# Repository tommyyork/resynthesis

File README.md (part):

# Resynthesis

This example implements a resynthesis effect for the Electro-Smith Daisy Patch.Init(), initially inspired by [the All Electric Smart Grid project](https://github.com/jvictor0/theallelectricsmartgrid) but it grew towards a granular direction as I added additional processing / while iterating on the output sounds. **This is maybe 90% GPT (🤖), 10% human, so buyer beware if you fork this or use this code.** There are plenty of bugs.

The panel design has most of the development hours, I wanted to procedurally generate it from the KiCad files for Patch.Init():

I've sent this off to the fab, and will make any updates once I've test fitted it on my actual Patch.Init(). Those labels for the pots may be too low...

The panel generation code could pretty easily be adapted to generate panels for any synth module, though the drill diameters and tolerances are currently hardcoded and basically tailored for the jacks / pots / switches you see in many Eurorack modules. The background pattern-to-pattern interpolation... I wish I could take credit. See [the agent session](AGENT_SESSION.md) for the blow by blow on how that came to be.

Incoming audio is analyzed into overlapping FFT grains, processed spectrally (phase propagation, V/OCT pitch, spectral flattening, bright/dark tilt, sparsity, and phase diffusion), and resynthesized with overlap-add back to the output. The V/OCT input (0–10 V) sets the fundamental frequency so the module can be used as an oscillator in a bass patch.

### Offline tests vs hardware signal path

The offline tests under `test/` are designed for **analysis and regressions**, not for level‑matched listening against the live module:

- **V/OCT harmonic tests (`make voct`, `test/test_resynth_voct.cpp`)**  
  - The processed passes are rendered **100% wet** with **no dry mix, no compressor, and no soft clip**.  
  - Grains are normalized only by hop size and active‑grain count, which keeps the **internal DSP stable** but typically yields WAVs that are **much quieter than the dry input**.  
  - This is intentional: the goal is **stable spectra and reliable note detection** (CSV/SVG analysis, suggested‑note checks), not loudness parity with the original sample or with the hardware output.

- **Harmonic engine tests (`make samples` → `test_resynth_harmonic`, `out/harmonic/*.wav`)**  
  - These also run the simplified harmonic resynth engine **fully wet** without the Patch‑SM output chain (no OFFER dry path, no post‑clip compressor, no panel‑driven MAX COMP).  
  - As a result, the harmonic test WAVs can also sit **significantly below** the level of the source material even though the spectra and pitch tracking match the intended behaviour.

- **Hardware firmware (`Resynthesis.cpp`)**  
  - On the Daisy Patch SM, the same core engine is wrapped in a **full output path**: OFFER dry/wet crossfade, hop/overlap‑aware wet gain smoothing, **smoothing‑dependent loudness compensation**, **soft clipping**, and a **fixed compressor/optional MAX COMP** stage.  
  - This chain is where the “finished instrument” loudness lives; the offline tests intentionally **omit** it so they can focus on **spectral behaviour, pitch stability, and CV‑to‑pitch mapping**.

If you A/B the `make voct` / harmonic WAVs against the original samples or the hardware output, expect them to be **significantly quieter**; treat them as **analysis fixtures**, not as loudness‑matched renderings of the module.

## Title: 化 (huà)

The panel uses the single character **化** (*huà*) as its primary title, from the *Daodejing* (道德經) in the sense of **transformation**—the change of one state into another, as in the phrase **化而欲作** (*huà ér yù zuò*, “when transformation arises, desire stirs”; ch. 37). Here it evokes the transformation of incoming sound through the phase vocoder into new timbres and textures.

**Panel typography:** All panel text is set in **all caps** using the open-source DIN-style font **[Gidole](https://github.com/larsenwork/Gidole)** (OFL licence; also available via [Google Fonts](https://fonts.google.com/specimen/Gidole)). The SVG uses the `Gidole` font family with fallbacks (DIN Alternate, DIN 2014, sans-serif) so the panel renders correctly even if Gidole is not installed.

## Make Targets

- **`make` / `make all`**: Build everything for this project (no tests are run): `libDaisy`, `DaisySP`, the `Resynthesis` firmware, host test binaries in `test/`, panel preview PNGs, and the SVG/PDF block‑diagram documentation.
- **`make program`**: Flash the built firmware image to the connected Daisy Patch SM.
- **`make openocd`**: Start OpenOCD for JTAG/SWD debug sessions.
- **`make debug`**: Build a debug firmware image and launch a GDB session against OpenOCD (with logging enabled as described below).
- **`make panel`**: Generate high‑resolution PNG previews of the front‑panel art in `panel/ResynthesisPanel.png` and `panel/ResynthesisPanel_eurorack_overlay.png` (requires Inkscape).
- **`make svg`**: Generate the US Letter block diagram of the audio path in `doc/Resynthesis_BlockDiagram_USLetter.pdf` and `doc/Resynthesis_BlockDiagram_USLetter.svg` (requires Graphviz `dot`).
- **`make test_resynth`**: Build and run the offline V/OCT sweep test; outputs WAVs into `test/out/voct_sweep/`.
- **`make test_cv_sweeps`**: Build and run the CV parameter sweep tests; outputs WAVs into `test/out/cv_sweep/` and `test/out/cv_sweep_maxcomp/`.
- **`make test_panel`**: Run the panel alignment / mechanical checks in `panel/test_panel_alignment.py`.
- **`make tests`**: Run the full test suite (`test_resynth`, `test_cv_sweeps`, and `test_panel`), regenerating WAVs under `test/out/`.
- **`make clean`**: Remove build artifacts and generated assets for this project (host test binaries, `test/out` WAVs, panel PNGs, and block‑diagram PDF/SVG/DOT files).

## Controls and panel mapping

This section is the **source of truth for panel labels and control behaviour**. Labels assume the **default CV bank** (no swapping).

### Potentiometers (CV_1–CV_4)

- **CV_1 – OFFER – send + dry/wet (panel: `OFFER`)**  
  Combined send and mix control for the resynthesis engine. **Fully CCW**, the output is **purely dry input** (non‑pitch‑shifted), and the engine effectively stops seeding new grains, so if no grains are currently active you hear a clean bypass. As you turn toward **12 o’clock**, the input is increasingly **“offered” to the grain engine** while a crossfade brings in the wet signal; around noon you get roughly **half dry, half wet** with the input actively feeding grains. **Fully CW** behaves like a **full send into the resynth path** so the output is dominated by loud, fully wet grains.  
  When **PITCH LOCK is on**, OFFER additionally becomes a **“pitch crossfade”**: CCW you hear the original, unshifted input; CW you hear a **clearly pitched, harmonically focused granular reconstruction** whose fundamental and partials follow the V/OCT voltage and **COLOR** setting, with most of the grain energy collapsing onto those harmonic families. Sweeping OFFER from CCW → CW in this case moves smoothly from dry, unshifted audio into the **fully pitch‑shifted, harmonically reinforced voice**, while existing grains are still allowed to **decay naturally** when you come back toward CCW.

- **CV_2 – Time‑Stretch / Grain Density (panel: `TIMESTRETCH`)**
  Bipolar control around 1× time. This knob controls how quickly grains are launched relative to the analysis hop: **left of centre** slows down and smears the audio into super‑slow, cloud‑like textures, while **right of centre** increases grain density and motion up into fast, chattery clusters. The mapping mirrors the TIME CV input so that the **0 V / noon region** covers the most musically useful 0.25×–4× range, with more extreme slow/fast behaviour toward the ends of travel.

- **CV_3 – FLUFF – granular cloud depth (panel: `FLUFF`)**  
  Sequentially enables a set of increasingly strong “cloud” behaviours in the grains. **Fully CCW** gives the most subtle, stable sound. As you turn clockwise, the engine adds:  
  1. Extra frequency‑dependent phase diffusion on top of CV_8.  
  2. Random jitter of the analysis window within each grain (time smearing) for a denser cloud.  
  3. Micro‑pitch jitter per grain in **pitch‑locked mode** (a few cents of movement around the target note).  
  4. Per‑bin magnitude jitter for a noisy, dense cloud at fully CW.  
  Existing spectral‑energy normalization keeps level changes musical across settings.

- **CV_4 – Color – bright/dark tilt, harmonic & frequency character (panel: `COLOR`)**  
  Three roles:
  - **Spectral tilt:** Negative values darken (emphasize low bins), positive values brighten (emphasize high bins); tilt gain is clamped so extremes do not clip or go silent.  
  - **Harmonic character in both modes (whenever PITCH LOCK is on):** **Color** selects which harmonic family is reinforced in **both** pitch‑locked and partial‑based modes using a **12‑harmonic scaffold** built on the V/OCT fundamental. **Fully CCW** emphasises the **even harmonics** \(2nd, 4th, 6th, … up to 12th\); around **noon** you get a more neutral mix; near **3 o’clock** and beyond the scaffold leans harder into the **odd harmonics**. Power is **front‑loaded into the low harmonics** and then tapered so that roughly the first four harmonics carry most of the added energy and higher harmonics contribute a progressively smaller, more textural sheen. In pitch‑locked mode the scaffold is gentler so the pitched grains stay dominant; in partial‑based mode the scaffold is more forward so simple inputs behave like a full synth voice. Reinforced partials use moderate, tapered gains so they **blend with the resynthesized body** rather than sounding like separate oscillators.  
  - **Pitch vs frequency shifting crossfade:** With PITCH LOCK on, the audio now passes through a dedicated **shifting block** immediately after the input. This block first **detects the incoming pitch** using a harmonic‑comb analyser (refactored from the offline V/OCT tests) and **pitch‑shifts** the input so its fundamental lands on the V/OCT‑selected note *before* any phase‑vocoder processing. As COLOR moves from roughly **3 o’clock to fully CW**, the block smoothly **fades from this pitch‑shifting process into a Bode‑style frequency shifter** whose shift rate also follows V/OCT. Fully CW gives a distinctly **frequency‑shifted, sideband‑style texture** feeding the resynth engine; backing off toward 3 o’clock restores more of the classic pitch‑locked behaviour.

### Toggles (B_7, B_8)

- **B_8 – PITCH LOCK (panel: `PITCH` / `LOCK`)**  
  Mode switch between **pitch‑locked grains** and a **partial‑based spectral model**:
  - **B_8 off – Partial‑based / spectral model mode**: Treats the incoming spectrum as a timbral template. Analysis bins stay at their original pitch; a **harmonic scaffold** (fundamental + harmonics) tuned to the **V/OCT** fundamental is overlaid with moderate gain so simple inputs behave like a full synth voice. **Color (CV_4)** selects the balance of odd vs even harmonics.  
  - **B_8 on – Pitch‑locked grains**: The phase‑vocoder pitch shifter locks each grain so its spectrum follows the V/OCT fundamental. This behaves more like a traditional pitched oscillator with the input acting as a complex waveform; the **same harmonic scaffold** is now applied more gently on top, reinforcing the chosen harmonic family without overwhelming the pitch‑corrected grains.

- **B_7 – MAX COMP (panel: `MAX` / `COMP`)**  
  Toggles a **stronger “MAX COMP” output compressor** after the resynth engine:
  - **Hardware:** B_7 is a **momentary pushbutton**, but the firmware treats it as a **software toggle**: each press flips the MAX COMP state between off and on.  
  - **B_7 off – Normal compression**: A gentle **2:1 feedforward compressor** (threshold ≈ -12 dB, modest make‑up gain) keeps levels musical and consistent as a sound source without being too squashy.  
  - **B_7 on – MAX COMP**: A more aggressive **Omnipressor‑style setting** (negative ratio, higher make‑up gain) that keeps average loudness high and brings out quiet material; this matches the “MAX COMP” path used in the offline CV sweep tests (`test/out/cv_sweep_maxcomp/`). When MAX COMP is active, the **front‑panel status LED above the jacks blinks at roughly 1 Hz** to indicate that the software toggle is engaged.

### CV inputs (CV_5–CV_8, middle jack row)

The middle jack row (panel labels above the jacks) is:

- `V/OCT`, `SMOOTH`, `SPARSITY`, *`D`* (diffusion)

Mapped controls:

- **CV_5 – V/OCT (panel: `V/OCT`, 0–10 V, 1 V/oct)**  
  Volt‑per‑octave pitch control. In both modes the algorithm resynthesizes the input around a musical fundamental set by this voltage (e.g. 1 V ≈ 32.7 Hz / C1, 2 V ≈ 65.4 Hz / C2). In **pitch‑locked mode** the new **shifting block** and the phase‑vocoder engine both treat this as the target note: the block first **shifts the raw input** so its detected fundamental lands on the requested V/OCT pitch, and the phase‑vocoder then follows that same fundamental when mapping grains; in **partial‑based mode** the original spectrum stays nearer its analysed pitch while a more forward harmonic scaffold (fundamental + harmonics) is overlaid at the V/OCT frequency.  
  With PITCH LOCK on and OFFER turned up, the combination of the shifting block and harmonic scaffold now **focuses most of the spectral energy into the fundamental and harmonics implied by V/OCT and COLOR** so the result is a **grainy but clearly pitched voice** rather than a diffuse, purely formant‑style texture. At the very top of COLOR, that same V/OCT value instead drives the **frequency‑shift amount** in the Bode‑style shifter, giving inharmonic, sideband‑rich tones feeding the resynth stage. 0 V = C0 (~16.35 Hz); 10 V is internally clamped near the upper range.

- **CV_6 – Magnitude Smoothing (panel: `SMOOTH`, bipolar, -5 V to +5 V)**  
  Controls how quickly spectral magnitudes follow the input. **Low** voltages track transients closely (crisp, articulate); **high** voltages smear dynamics into a pad‑like magnitude envelope. The engine’s **default** smoothing is now around **0.2**, which keeps transients present while still allowing the adaptive smoothing stages to build a stable, cloud‑like body at higher settings.

- **CV_7 – Spectral Sparsity (panel: `SPARSITY`, bipolar, -5 V to +5 V)**  
  Bipolar control mapped to the full **0–1** sparsity range (0 V ≈ 0.5). Lower values keep most bins active and sound fuller; higher values keep only the strongest bins, leading to more pronounced, metallic / ring‑mod‑like spectra, with internal energy preservation so results stay present rather than simply “thin”.

- **CV_8 – Phase Diffusion (panel: italic `D`, bipolar, -5 V to +5 V)**  
  Bipolar control mapped to the full **0–1** diffusion range (0 V ≈ 0.5). Lower values keep phases more coherent (clearer tone); higher values introduce strong randomization for noisy, cloud‑like, frequency‑shift‑ish textures. **FLUFF (CV_3)** can add extra diffusion on top of this control.

### CV outputs (CV_OUT_1, CV_OUT_2)

- **CV_OUT_1 / C10 – THOUGHTS (panel: lightning bolt symbol `⚡`)**  
  CV jack directly beneath the COLOR knob (top‑right of the middle‑switch/jack cluster).  
  - **Signal:** A **chaotic, Brownian‑like CV** that wanders in a musically bounded way between 0–5 V. Its motion becomes **wider and quicker** when the input is loud and harmonically rich, and **slower and more restrained** when the input is quieter and more noise‑like or spectrally flat.  
  - **Construction:** Internally, THOUGHTS is driven by a **logistic‑map–style chaotic system**. Each audio frame, the engine measures both a smoothed spectral‑energy value and a simple **harmonic peakiness metric** (how “spiky” the spectrum is relative to its mean). These two features form an **excitement** value that modulates the chaotic map’s parameter and effective step rate, then the result is centered, range‑scaled by excitement, and gently low‑pass filtered before being mapped to 0–5 V.  
  - **Musical uses:** Because THOUGHTS reacts to both loudness and harmonic structure but with an internal chaotic drift, it behaves as an **interesting, somewhat tangential CV source**: ideal for slowly moving filter cutoffs, effect depths, wavefolder thresholds, or other processors that you want to “breathe” with the resynth texture without being a simple envelope follower. High‑energy, harmonic material produces animated, complex CV excursions; sparse or dark inputs yield smaller, slower meanders that still feel alive.

- **CV_OUT_2 – Grain energy meter + MAX COMP status / LED driver (no dedicated panel label)**  
  Drives the **front‑panel status LED** (row “LED (status)” in the jack/part mapping table) and exposes a **0–5 V envelope of the grain engine’s activity**, with a **MAX COMP blink overlay**:  
  - **Base behaviour (MAX COMP off):** CV_OUT_2 follows the current **grain / spectral energy** of the resynthesis engine, mapped into **0–5 V**. Quiet, sparse material produces a dim LED / low CV; louder, denser inputs push the LED and CV level towards 5 V.  
  - **MAX COMP on (software toggle engaged):** The same grain‑energy envelope continues to drive CV_OUT_2, but a **logic‑style overlay blinks the output at full intensity (~1.5 Hz)** to show that MAX COMP is active. During the “on” phase of the blink the output is forced to **5 V**; during the “off” phase it returns to the underlying grain‑energy level.  
  This output is intended primarily for the on‑panel LED, but you can patch it elsewhere either as a **grain‑energy envelope follower** or as a **MAX COMP activity indicator**. Its behaviour is independent of **THOUGHTS (CV_OUT_1)**, which continues to carry the separate chaotic CV derived from the same internal analysis.

### Jacks: gates, CVs, and audio I/O

Panel jack layout (from top row to bottom row; labels are **over** each jack and centered):

- **Top row** (4 jacks): `B10`, `B9`, `B5`, `B6` — gate inputs/outputs.
- **Middle row** (4 jacks): `V/OCT` (CV_5), *`t`* / TIME (CV_6), `SPARSITY` (CV_7), *`D`* / diffusion (CV_8).
- **Bottom row** (4 jacks): `IN L`, `IN R`, `OUT L`, `OUT R` — stereo audio inputs and outputs. The two middle jacks are also **CV_OUT_1** and **CV_OUT_2** in firmware.

### Stereo inputs and outputs

- **IN L / IN R (bottom row, left two jacks; panel: `IN L`, `IN R`)**  
  Audio inputs mapped to firmware channels `IN_L` and `IN_R`. They feed the analysis stage of the phase vocoder; typical use is a stereo source (e.g. a loop, synth, or external instrument).

- **OUT L / OUT R (bottom row, right two jacks; panel: `OUT L`, `OUT R`)**  
  Audio outputs mapped to firmware channels `OUT_L` and `OUT_R`. Carry the fully processed resynth signal after shaping, overlap‑add synthesis, soft clipping, and final compressor. Useful both as **effect returns** and as a standalone stereo sound source when driven from V/OCT.

## Panel

### Files

- **`panel/output/ResynthesisPanel.svg`**  
  Vector artwork of a 3U x 10HP Eurorack panel: height **128.5 mm**, width **50.8 mm**. All graphics and drill holes are in millimetres. **Generated by** `panel/_deprecated_generate_panel.py` (or `panel/generate_panel_kicad.py`).

- **`panel/output/ResynthesisPanel.jpg`**  
  Single panel preview image for quick visual reference. Generated from `ResynthesisPanel.svg` by `make panel` (requires Inkscape).

- **`panel/output/render_eurorack_overlay.py`**  
  Script that generates an **Eurorack standard overlay** SVG from any panel SVG: green dotted 2HP vertical grid, neon blue dotted rail‑center lines, neon pink (x, y) annotations at each cut center plus panel dimensions.

- **`panel/_deprecated_generate_panel.py`**  
  Deprecated Python script that generates the canonical `ResynthesisPanel.svg` (prefer `panel/generate_panel_kicad.py`). It encodes the full 3U × 10HP geometry, background artwork, all drill centres, the SD card holder cutout, and the four rectangular Eurorack mounting screw slots so they line up with the Doepfer / Gie‑Tec rail standard (3 mm from the top and bottom edges; see `panel/eurorack_spec/README.md`).

### Input / jack mapping (KiCad PCB → panel)

The table below ties together the **Resynthesis panel labels**, the **Patch.Init default panel silkscreen**, the **KiCad schematic references**, and the mechanical information from the KiCad footprints. Positions are given in KiCad PCB coordinates (millimetres) taken from `panel/KiCad_PCB/ES_Daisy_Patch_SM_FB_Rev1.kicad_pcb`.

| Resynthesis label   | Patch.Init panel label | Component type          | Panel hole Ø (mm) | PCB X (mm) | PCB Y (mm) | KiCad schematic ref | Footprint filename                  |
|---------------------|------------------------|-------------------------|-------------------|------------|------------|----------------------|-------------------------------------|
| B10 (gate in 1)     | B10                    | S_JACK                  | 6.2               | 130.251    | 125.316    | J_GATEIN1            | `S_JACK.kicad_mod`                  |
| B9 (gate in 2)      | B9                     | S_JACK                  | 6.2               | 142.418    | 125.316    | J_GATEIN2            | `S_JACK.kicad_mod`                  |
| B5 (gate out 1)     | B5                     | S_JACK                  | 6.2               | 154.584    | 125.316    | J_GATEOUT1           | `S_JACK.kicad_mod`                  |
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
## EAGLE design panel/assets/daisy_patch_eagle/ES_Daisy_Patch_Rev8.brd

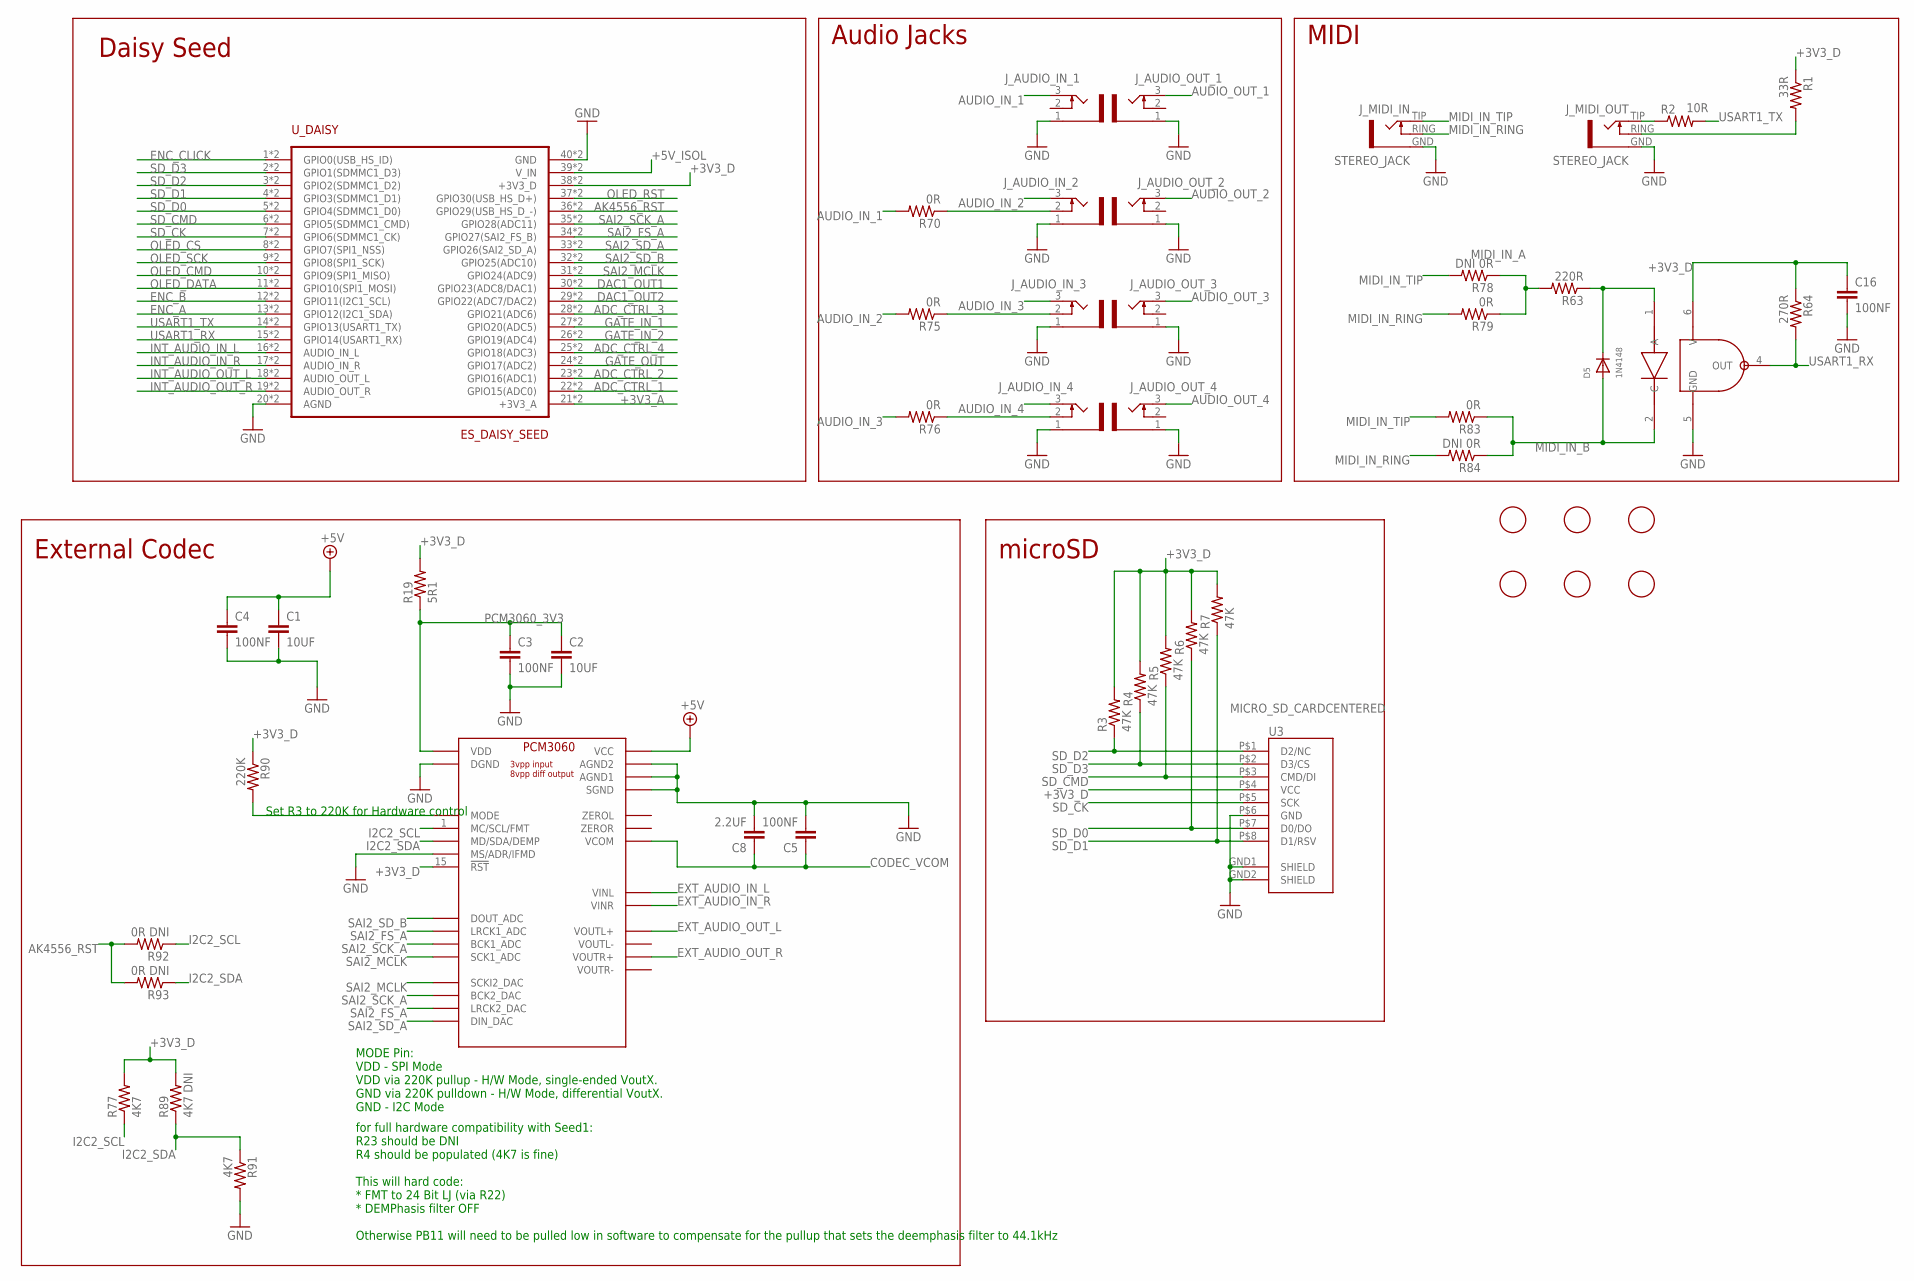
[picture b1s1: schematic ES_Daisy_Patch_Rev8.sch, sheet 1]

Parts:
C1, C2: 10UF; C0805
C3, C4, C5, C16: 100NF; C0402
C8: 2.2UF; C0603
D5: 1N4148; SOD-323F
FD1, FD2, FD3, FD4, FD5, FD6: FIDUCIAL; FIDUCIAL_1MM
J_AUDIO_IN_1, J_AUDIO_IN_2, J_AUDIO_IN_3, J_AUDIO_IN_4: EURO_JACK_SMT; SMT_JACK
J_AUDIO_OUT_1, J_AUDIO_OUT_2, J_AUDIO_OUT_3, J_AUDIO_OUT_4: EURO_JACK_SMT; SMT_JACK
J_MIDI_IN: STEREO_JACK; STEREO_JACK_3.5MM
J_MIDI_OUT: STEREO_JACK; STEREO_JACK_3.5MM
R1: 33R; R0603
R2: 10R; R0603
R3, R4, R5, R6, R7: 47K; R0603
R19: 5R1; R0603
R63: 220R; R0603
R64: 270R; R0603
R70, R75, R76, R79, R83: 0R; R0603
R77, R91: 4K7; R0603
R78, R84: DNI 0R; R0603
R89: 4K7 DNI; R0603
R90: 220K; R0603
R92, R93: 0R DNI; R0603
U1: PCM3060; TSSOP-28
U3: MICRO_SD_CARDCENTERED; VERT_MICROSD_CENTERED
U15: OPTOISOLATOR_H11L1M; DIL06_GULLWING
U_DAISY: ES_DAISY_SEED; ES_DAISY_SEED_DOUBLE

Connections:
+3V3_A: U_DAISY.21 (+3V3_A), U_DAISY.B21 (+3V3_A); also elsewhere on the board
+3V3_D: C16.1, R1.1, R3.2, R4.2, R5.2, R6.2, R7.2, R19.2, R64.1, R77.2, R89.2, R90.1, U1.15 (!RST), U3.P$4 (VCC), U15.6 (V), U_DAISY.38 (+3V3_D), U_DAISY.B38 (+3V3_D); also elsewhere on the board
+5V: C1.1, C4.1, U1.24 (VCC); also elsewhere on the board
+5V_ISOL: U_DAISY.39 (V_IN), U_DAISY.B39 (V_IN); also elsewhere on the board
ADC_CTRL_1: U_DAISY.22 (GPIO15(ADC0)), U_DAISY.B22 (GPIO15(ADC0)); also elsewhere on the board
ADC_CTRL_2: U_DAISY.23 (GPIO16(ADC1)), U_DAISY.B23 (GPIO16(ADC1)); also elsewhere on the board
ADC_CTRL_3: U_DAISY.28 (GPIO21(ADC6)), U_DAISY.B28 (GPIO21(ADC6)); also elsewhere on the board
ADC_CTRL_4: U_DAISY.25 (GPIO18(ADC3)), U_DAISY.B25 (GPIO18(ADC3)); also elsewhere on the board
AK4556_RST: R92.2, R93.2, U_DAISY.36 (GPIO29(USB_HS_D_-)), U_DAISY.B36 (GPIO29(USB_HS_D_-))
AUDIO_IN_1: J_AUDIO_IN_1.3 (TIP), R70.2; also elsewhere on the board
AUDIO_IN_2: J_AUDIO_IN_2.3 (TIP), R75.2; also elsewhere on the board
AUDIO_IN_3: J_AUDIO_IN_3.3 (TIP), R76.2; also elsewhere on the board
AUDIO_IN_4: J_AUDIO_IN_4.3 (TIP); also elsewhere on the board
AUDIO_OUT_1: J_AUDIO_OUT_1.3 (TIP); also elsewhere on the board
AUDIO_OUT_2: J_AUDIO_OUT_2.3 (TIP); also elsewhere on the board
AUDIO_OUT_3: J_AUDIO_OUT_3.3 (TIP); also elsewhere on the board
AUDIO_OUT_4: J_AUDIO_OUT_4.3 (TIP); also elsewhere on the board
CODEC_VCOM: C5.1, C8.1, U1.21 (VCOM); also elsewhere on the board
DAC1_OUT1: U_DAISY.30 (GPIO23(ADC8/DAC1)), U_DAISY.B30 (GPIO23(ADC8/DAC1)); also elsewhere on the board
DAC1_OUT2: U_DAISY.29 (GPIO22(ADC7/DAC2)), U_DAISY.B29 (GPIO22(ADC7/DAC2)); also elsewhere on the board
ENC_A: U_DAISY.13 (GPIO12(I2C1_SDA)), U_DAISY.B13 (GPIO12(I2C1_SDA)); also elsewhere on the board
ENC_B: U_DAISY.12 (GPIO11(I2C1_SCL)), U_DAISY.B12 (GPIO11(I2C1_SCL)); also elsewhere on the board
ENC_CLICK: U_DAISY.1 (GPIO0(USB_HS_ID)), U_DAISY.B1 (GPIO0(USB_HS_ID)); also elsewhere on the board
EXT_AUDIO_IN_L: U1.25 (VINL); also elsewhere on the board
EXT_AUDIO_IN_R: U1.26 (VINR); also elsewhere on the board
EXT_AUDIO_OUT_L: U1.20 (VOUTL+); also elsewhere on the board
EXT_AUDIO_OUT_R: U1.18 (VOUTR+); also elsewhere on the board
GATE_IN_1: U_DAISY.27 (GPIO20(ADC5)), U_DAISY.B27 (GPIO20(ADC5)); also elsewhere on the board
GATE_IN_2: U_DAISY.26 (GPIO19(ADC4)), U_DAISY.B26 (GPIO19(ADC4)); also elsewhere on the board
GATE_OUT: U_DAISY.24 (GPIO17(ADC2)), U_DAISY.B24 (GPIO17(ADC2)); also elsewhere on the board
GND: C1.2, C2.2, C3.2, C4.2, C5.2, C8.2, C16.2, J_AUDIO_IN_1.1 (GND), J_AUDIO_IN_2.1 (GND), J_AUDIO_IN_3.1 (GND), J_AUDIO_IN_4.1 (GND), J_AUDIO_OUT_1.1 (GND), J_AUDIO_OUT_2.1 (GND), J_AUDIO_OUT_3.1 (GND), J_AUDIO_OUT_4.1 (GND), J_MIDI_IN.GND, J_MIDI_OUT.GND, R91.2, U1.8 (DGND), U1.16 (SGND), U1.22 (AGND2), U1.23 (AGND1), U1.27 (MS/ADR/IFMD), U3.GND1 (SHIELD), U3.GND2 (SHIELD), U3.P$6 (GND), U15.5 (GND), U_DAISY.20 (AGND), U_DAISY.40 (GND), U_DAISY.B20 (AGND), U_DAISY.B40 (GND); also elsewhere on the board
I2C2_SCL: R77.1, R92.1, U1.1 (MC/SCL/FMT)
I2C2_SDA: R89.1, R91.1, R93.1, U1.2 (MD/SDA/DEMP)
INT_AUDIO_IN_L: U_DAISY.16 (AUDIO_IN_L), U_DAISY.B16 (AUDIO_IN_L); also elsewhere on the board
INT_AUDIO_IN_R: U_DAISY.17 (AUDIO_IN_R), U_DAISY.B17 (AUDIO_IN_R); also elsewhere on the board
INT_AUDIO_OUT_L: U_DAISY.18 (AUDIO_OUT_L), U_DAISY.B18 (AUDIO_OUT_L); also elsewhere on the board
INT_AUDIO_OUT_R: U_DAISY.19 (AUDIO_OUT_R), U_DAISY.B19 (AUDIO_OUT_R); also elsewhere on the board
MIDI_IN_A: R63.2, R78.1, R79.1
MIDI_IN_B: D5.A, R83.1, R84.1, U15.2 (C)
MIDI_IN_RING: J_MIDI_IN.RING (NORM), R79.2, R84.2
MIDI_IN_TIP: J_MIDI_IN.TIP, R78.2, R83.2
unnamed: J_MIDI_OUT.TIP, R2.1
unnamed: J_MIDI_OUT.RING (NORM), R1.2
unnamed: J_AUDIO_IN_2.2 (NORM), R70.1
unnamed: J_AUDIO_IN_3.2 (NORM), R75.1
unnamed: J_AUDIO_IN_4.2 (NORM), R76.1
unnamed: R90.2, U1.28 (MODE)
unnamed: D5.C, R63.1, U15.1 (A)
OLED_CMD: U_DAISY.10 (GPIO9(SPI1_MISO)), U_DAISY.B10 (GPIO9(SPI1_MISO)); also elsewhere on the board
OLED_CS: U_DAISY.8 (GPIO7(SPI1_NSS)), U_DAISY.B8 (GPIO7(SPI1_NSS)); also elsewhere on the board
OLED_DATA: U_DAISY.11 (GPIO10(SPI1_MOSI)), U_DAISY.B11 (GPIO10(SPI1_MOSI)); also elsewhere on the board
OLED_RST: U_DAISY.37 (GPIO30(USB_HS_D+)), U_DAISY.B37 (GPIO30(USB_HS_D+)); also elsewhere on the board
OLED_SCK: U_DAISY.9 (GPIO8(SPI1_SCK)), U_DAISY.B9 (GPIO8(SPI1_SCK)); also elsewhere on the board
PCM3060_3V3: C2.1, C3.1, R19.1, U1.7 (VDD)
SAI2_FS_A: U1.4 (LRCK1_ADC), U1.11 (LRCK2_DAC), U_DAISY.34 (GPIO27(SAI2_FS_B)), U_DAISY.B34 (GPIO27(SAI2_FS_B))
SAI2_MCLK: U1.6 (SCK1_ADC), U1.9 (SCKI2_DAC), U_DAISY.31 (GPIO24(ADC9)), U_DAISY.B31 (GPIO24(ADC9))
SAI2_SCK_A: U1.5 (BCK1_ADC), U1.10 (BCK2_DAC), U_DAISY.35 (GPIO28(ADC11)), U_DAISY.B35 (GPIO28(ADC11))
SAI2_SD_A: U1.12 (DIN_DAC), U_DAISY.33 (GPIO26(SAI2_SD_A)), U_DAISY.B33 (GPIO26(SAI2_SD_A))
SAI2_SD_B: U1.3 (DOUT_ADC), U_DAISY.32 (GPIO25(ADC10)), U_DAISY.B32 (GPIO25(ADC10))
SD_CK: U3.P$5 (SCK), U_DAISY.7 (GPIO6(SDMMC1_CK)), U_DAISY.B7 (GPIO6(SDMMC1_CK))
SD_CMD: R5.1, U3.P$3 (CMD/DI), U_DAISY.6 (GPIO5(SDMMC1_CMD)), U_DAISY.B6 (GPIO5(SDMMC1_CMD))
SD_D0: R6.1, U3.P$7 (D0/DO), U_DAISY.5 (GPIO4(SDMMC1_D0)), U_DAISY.B5 (GPIO4(SDMMC1_D0))
SD_D1: R7.1, U3.P$8 (D1/RSV), U_DAISY.4 (GPIO3(SDMMC1_D1)), U_DAISY.B4 (GPIO3(SDMMC1_D1))
SD_D2: R3.1, U3.P$1 (D2/NC), U_DAISY.3 (GPIO2(SDMMC1_D2)), U_DAISY.B3 (GPIO2(SDMMC1_D2))
SD_D3: R4.1, U3.P$2 (D3/CS), U_DAISY.2 (GPIO1(SDMMC1_D3)), U_DAISY.B2 (GPIO1(SDMMC1_D3))
USART1_RX: R64.2, U15.4 (OUT), U_DAISY.15 (GPIO14(USART1_RX)), U_DAISY.B15 (GPIO14(USART1_RX))
USART1_TX: R2.2, U_DAISY.14 (GPIO13(USART1_TX)), U_DAISY.B14 (GPIO13(USART1_TX))

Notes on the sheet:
Daisy Seed
Audio Jacks
External Codec
MIDI
microSD
MODE Pin: VDD - SPI Mode VDD via 220K pullup - H/W Mode, single-ended VoutX. GND via 220K pulldown - H/W Mode, differential VoutX. GND - I2C Mode
Set R3 to 220K for Hardware control
for full hardware compatibility with Seed1: R23 should be DNI R4 should be populated (4K7 is fine) This will hard code: * FMT to 24 Bit LJ (via R22) * DEMPhasis filter OFF Otherwise PB11 will need to be pulled low in software to compensate for the pullup that sets the deemphasis filter to 44.1kHz

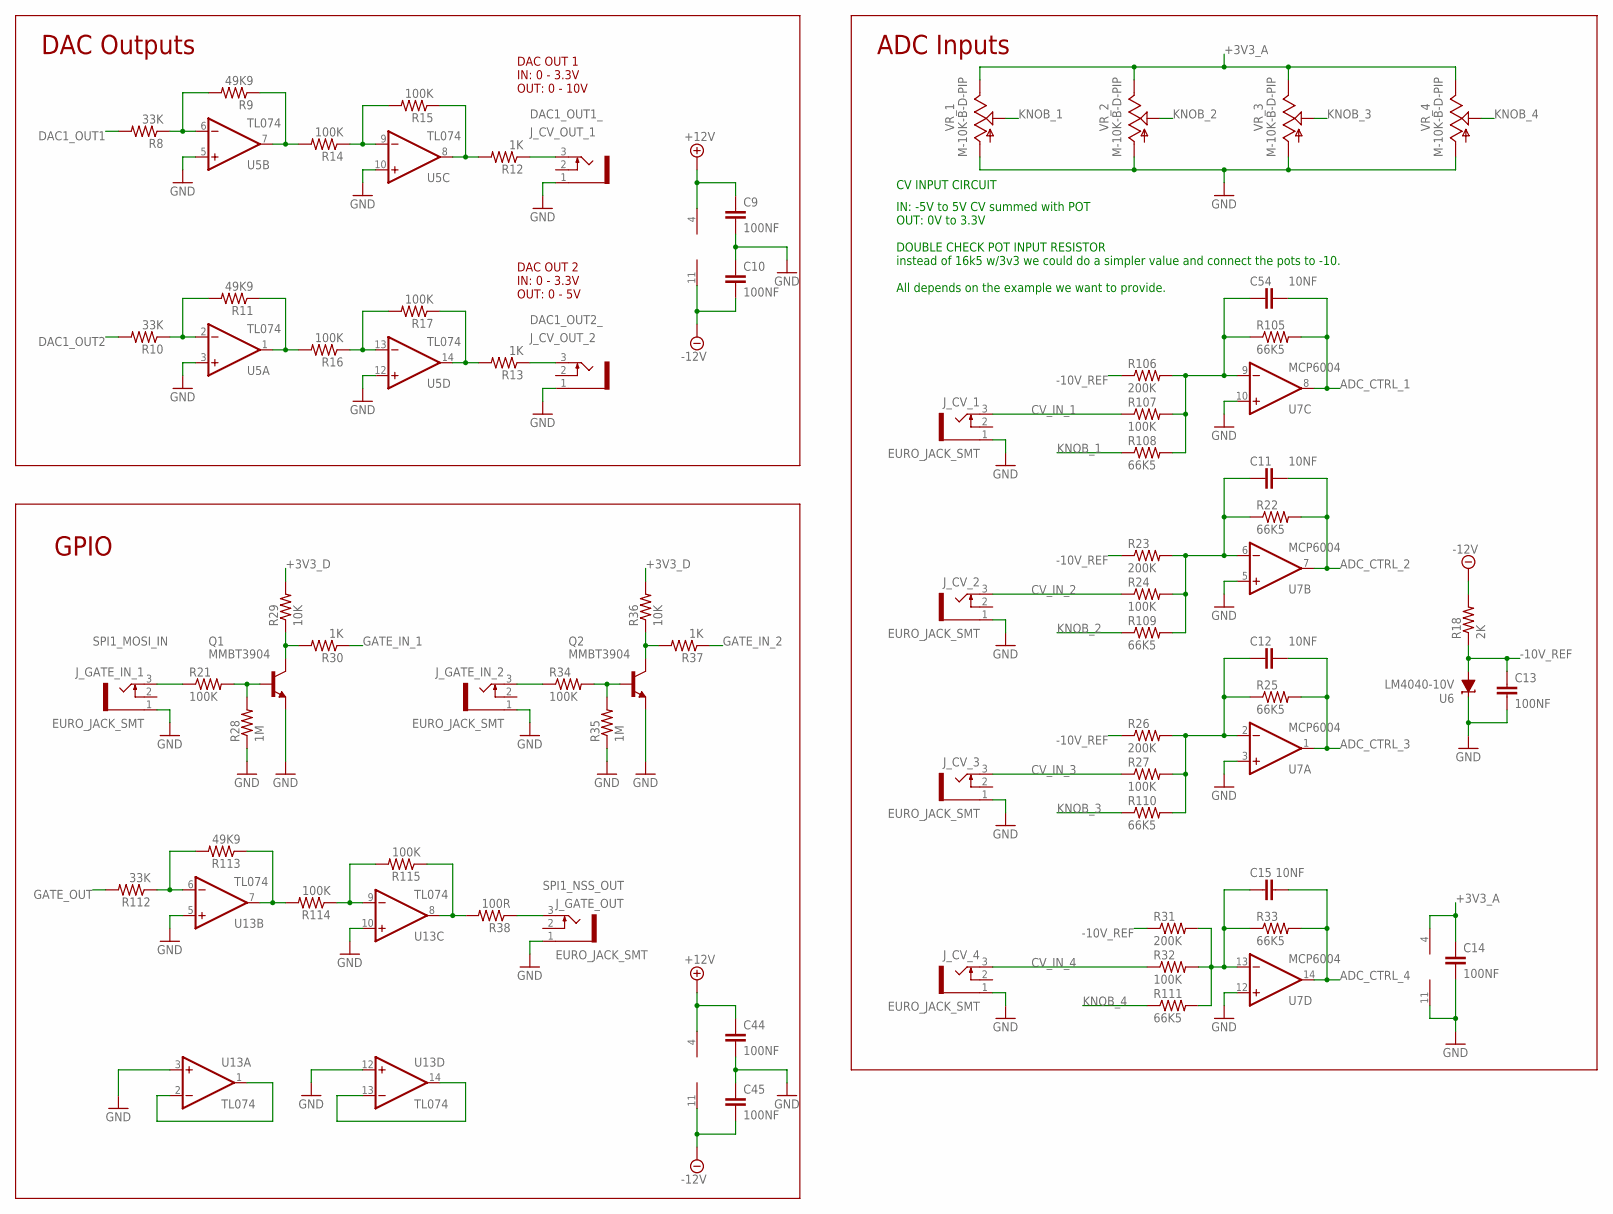
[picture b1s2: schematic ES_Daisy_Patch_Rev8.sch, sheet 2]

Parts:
C9, C10, C13, C14, C44, C45: 100NF; C0402
C11, C12, C15, C54: 10NF; C0603
J_CV_1, J_CV_2, J_CV_3, J_CV_4: EURO_JACK_SMT; SMT_JACK
J_CV_OUT_1, J_CV_OUT_2: EURO_JACK_SMT; SMT_JACK
J_GATE_IN_1, J_GATE_IN_2: EURO_JACK_SMT; SMT_JACK
J_GATE_OUT: EURO_JACK_SMT; SMT_JACK
Q1, Q2: MMBT3904; SOT23-BEC
R8, R10, R112: 33K; R0603
R9, R11, R113: 49K9; R0603
R12, R13, R30, R37: 1K; R0402
R14, R15, R16, R17, R21, R24, R27, R32, R34, R107, R114, R115: 100K; R0402
R18: 2K; R0603
R22, R25, R33, R105, R108, R109, R110, R111: 66K5; R0603
R23, R26, R31, R106: 200K; R0603
R28, R35: 1M; R0603
R29, R36: 10K; R0603
R38: 100R; R0603
U5, U13: TL074; TSSOP-14
U6: LM4040-10V; DBZ_R-PDSO-G3
U7: MCP6004; TSSOP-14
VR_1, VR_2, VR_3, VR_4: M-10K-B-D-PIP; PIP_POT_PASTE6

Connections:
+3V3_A: C14.1, U7.4 (V+), VR_1.3, VR_2.3, VR_3.3, VR_4.3; also elsewhere on the board
+3V3_D: R29.2, R36.2; also elsewhere on the board
+12V: C9.1, C44.1, U5.4 (V+), U13.4 (V+); also elsewhere on the board
-10V_REF: C13.1, R18.1, R23.1, R26.1, R31.1, R106.1, U6.2 (A)
-12V: C10.2, C45.2, R18.2, U5.11 (V-), U13.11 (V-); also elsewhere on the board
ADC_CTRL_1: C54.2, R105.2, U7.8 (OUT); also elsewhere on the board
ADC_CTRL_2: C11.2, R22.2, U7.7 (OUT); also elsewhere on the board
ADC_CTRL_3: C12.2, R25.2, U7.1 (OUT); also elsewhere on the board
ADC_CTRL_4: C15.2, R33.2, U7.14 (OUT); also elsewhere on the board
CV_IN_1: J_CV_1.3 (TIP), R107.1
CV_IN_2: J_CV_2.3 (TIP), R24.1
CV_IN_3: J_CV_3.3 (TIP), R27.1
CV_IN_4: J_CV_4.3 (TIP), R32.1
DAC1_OUT1: R8.2; also elsewhere on the board
DAC1_OUT1_: J_CV_OUT_1.3 (TIP), R12.1
DAC1_OUT2: R10.2; also elsewhere on the board
DAC1_OUT2_: J_CV_OUT_2.3 (TIP), R13.1
GATE_IN_1: R30.1; also elsewhere on the board
GATE_IN_2: R37.1; also elsewhere on the board
GATE_OUT: R112.2; also elsewhere on the board
GND: C9.2, C10.1, C13.2, C14.2, C44.2, C45.1, J_CV_1.1 (GND), J_CV_2.1 (GND), J_CV_3.1 (GND), J_CV_4.1 (GND), J_CV_OUT_1.1 (GND), J_CV_OUT_2.1 (GND), J_GATE_IN_1.1 (GND), J_GATE_IN_2.1 (GND), J_GATE_OUT.1 (GND), Q1.E, Q2.E, R28.1, R35.1, U5.3 (+IN), U5.5 (+IN), U5.10 (+IN), U5.12 (+IN), U6.1 (C), U7.3 (+IN), U7.5 (+IN), U7.10 (+IN), U7.11 (V-), U7.12 (+IN), U13.3 (+IN), U13.5 (+IN), U13.10 (+IN), U13.12 (+IN), VR_1.1, VR_2.1, VR_3.1, VR_4.1; also elsewhere on the board
KNOB_1: R108.1, VR_1.2
KNOB_2: R109.1, VR_2.2
KNOB_3: R110.1, VR_3.2
KNOB_4: R111.1, VR_4.2
unnamed: R14.1, R15.2, U5.9 (-IN)
unnamed: R12.2, R15.1, U5.8 (OUT)
unnamed: R8.1, R9.2, U5.6 (-IN)
unnamed: R9.1, R14.2, U5.7 (OUT)
unnamed: C54.1, R105.1, R106.2, R107.2, R108.2, U7.9 (-IN)
unnamed: R10.1, R11.2, U5.2 (-IN)
unnamed: R11.1, R16.2, U5.1 (OUT)
unnamed: R112.1, R113.2, U13.6 (-IN)
unnamed: R16.1, R17.2, U5.13 (-IN)
unnamed: R13.2, R17.1, U5.14 (OUT)
unnamed: U13.1 (OUT), U13.2 (-IN)
unnamed: R113.1, R114.2, U13.7 (OUT)
unnamed: R114.1, R115.2, U13.9 (-IN)
unnamed: R38.2, R115.1, U13.8 (OUT)
unnamed: Q1.C, R29.1, R30.2
unnamed: C11.1, R22.1, R23.2, R24.2, R109.2, U7.6 (-IN)
unnamed: Q2.B, R34.2, R35.2
unnamed: C12.1, R25.1, R26.2, R27.2, R110.2, U7.2 (-IN)
unnamed: Q1.B, R21.2, R28.2
unnamed: Q2.C, R36.1, R37.2
unnamed: C15.1, R31.2, R32.2, R33.1, R111.2, U7.13 (-IN)
unnamed: U13.13 (-IN), U13.14 (OUT)
SPI1_MISO_IN: J_GATE_IN_2.3 (TIP), R34.1
SPI1_MOSI_IN: J_GATE_IN_1.3 (TIP), R21.1
SPI1_NSS_OUT: J_GATE_OUT.3 (TIP), R38.1

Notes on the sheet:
DAC Outputs
DAC OUT 1 IN: 0 - 3.3V OUT: 0 - 10V
DAC OUT 2 IN: 0 - 3.3V OUT: 0 - 5V
ADC Inputs
GPIO
IN: -5V to 5V CV summed with POT OUT: 0V to 3.3V DOUBLE CHECK POT INPUT RESISTOR instead of 16k5 w/3v3 we could do a simpler value and connect the pots to -10. All depends on the example we want to provide.
CV INPUT CIRCUIT

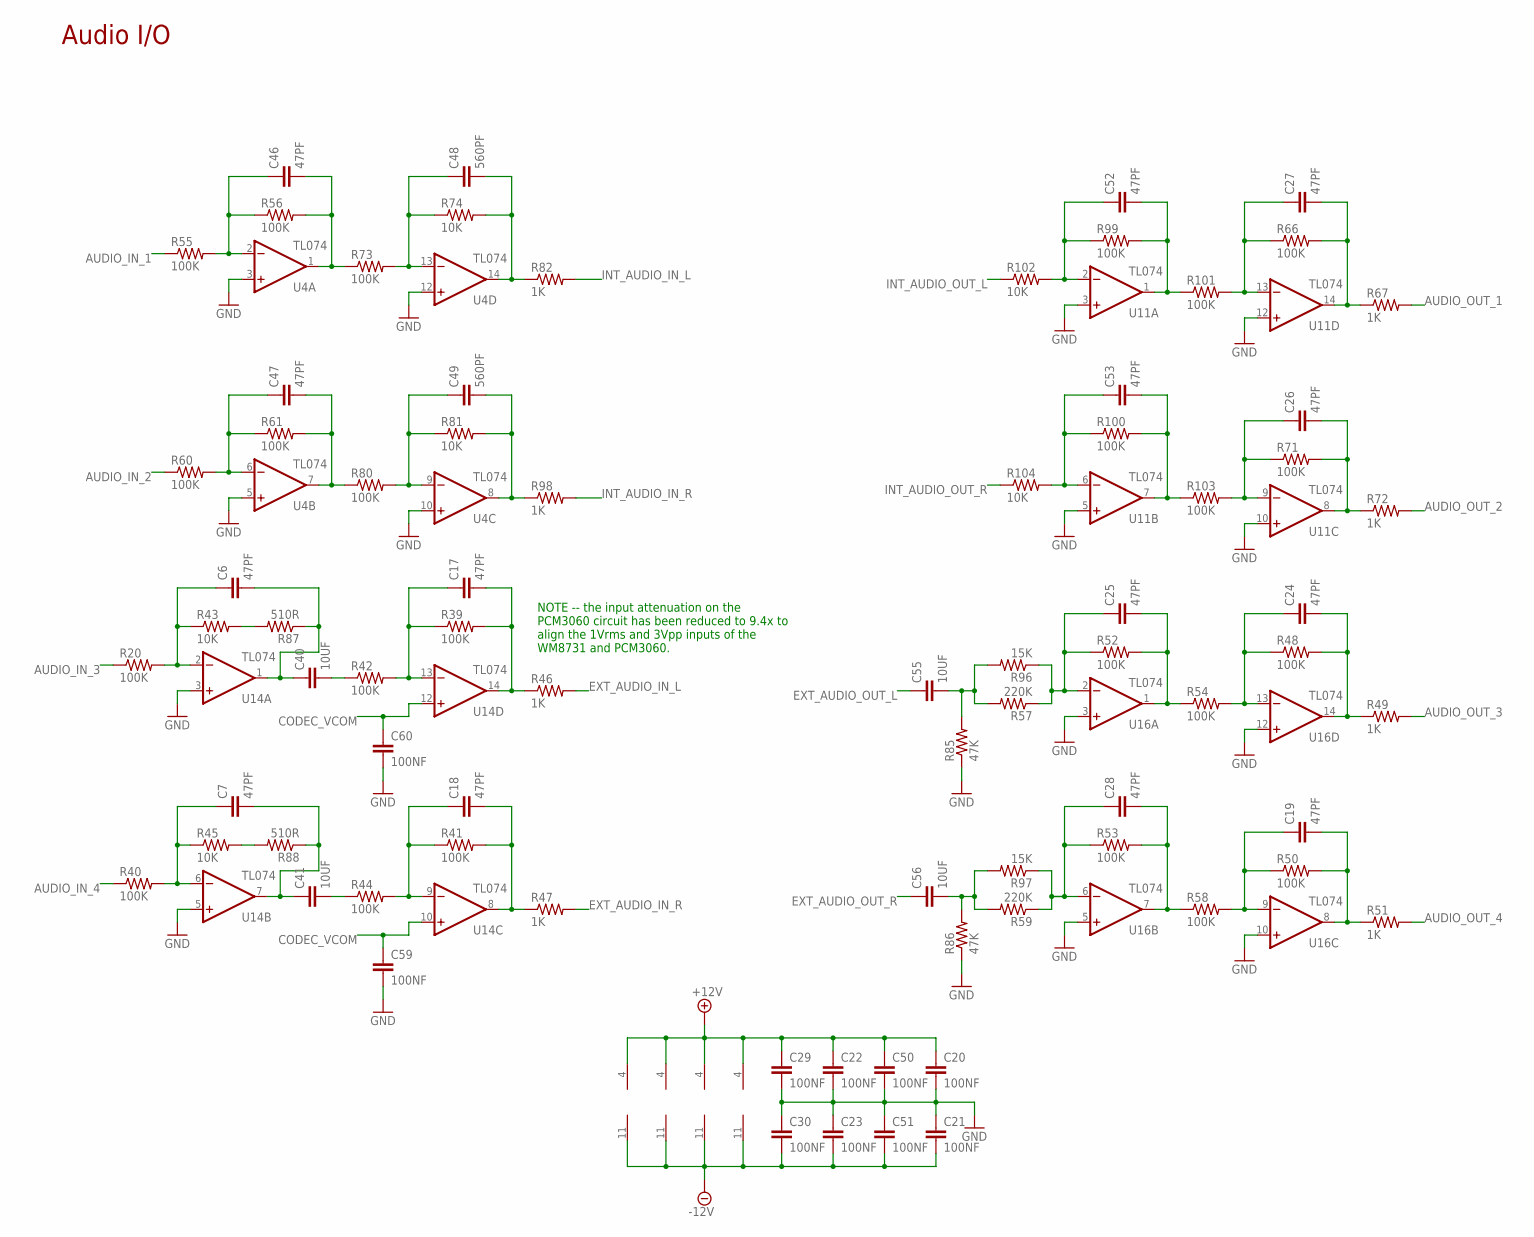
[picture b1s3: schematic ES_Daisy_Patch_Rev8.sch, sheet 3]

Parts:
C6, C7, C17, C18, C19, C24, C25, C26, C27, C28, C46, C47, C52, C53: 47PF; C0603
C20, C21, C22, C23, C29, C30, C50, C51, C59, C60: 100NF; C0402
C40, C41, C55, C56: 10UF; C0805
C48, C49: 560PF; C0603
R20, R39, R40, R41, R42, R44, R48, R50, R52, R53, R54, R55, R56, R58, R60, R61, R66, R71, R73, R80, R99, R100, R101, R103: 100K; R0402
R43, R45, R74, R81, R102, R104: 10K; R0603
R46, R47, R49, R51, R67, R72, R82, R98: 1K; R0402
R57, R59: 220K; R0603
R85, R86: 47K; R0603
R87, R88: 510R; R0603
R96, R97: 15K; R0603
U4, U11, U14, U16: TL074; TSSOP-14

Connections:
+12V: C20.1, C22.1, C29.1, C50.1, U4.4 (V+), U11.4 (V+), U14.4 (V+), U16.4 (V+); also elsewhere on the board
-12V: C21.2, C23.2, C30.2, C51.2, U4.11 (V-), U11.11 (V-), U14.11 (V-), U16.11 (V-); also elsewhere on the board
AUDIO_IN_1: R55.1; also elsewhere on the board
AUDIO_IN_2: R60.1; also elsewhere on the board
AUDIO_IN_3: R20.1; also elsewhere on the board
AUDIO_IN_4: R40.1; also elsewhere on the board
AUDIO_OUT_1: R67.2; also elsewhere on the board
AUDIO_OUT_2: R72.2; also elsewhere on the board
AUDIO_OUT_3: R49.2; also elsewhere on the board
AUDIO_OUT_4: R51.2; also elsewhere on the board
CODEC_VCOM: C59.1, C60.1, U14.10 (+IN), U14.12 (+IN); also elsewhere on the board
EXT_AUDIO_IN_L: R46.2; also elsewhere on the board
EXT_AUDIO_IN_R: R47.2; also elsewhere on the board
EXT_AUDIO_OUT_L: C55.1; also elsewhere on the board
EXT_AUDIO_OUT_R: C56.1; also elsewhere on the board
GND: C20.2, C21.1, C22.2, C23.1, C29.2, C30.1, C50.2, C51.1, C59.2, C60.2, R85.1, R86.1, U4.3 (+IN), U4.5 (+IN), U4.10 (+IN), U4.12 (+IN), U11.3 (+IN), U11.5 (+IN), U11.10 (+IN), U11.12 (+IN), U14.3 (+IN), U14.5 (+IN), U16.3 (+IN), U16.5 (+IN), U16.10 (+IN), U16.12 (+IN); also elsewhere on the board
INT_AUDIO_IN_L: R82.2; also elsewhere on the board
INT_AUDIO_IN_R: R98.2; also elsewhere on the board
INT_AUDIO_OUT_L: R102.1; also elsewhere on the board
INT_AUDIO_OUT_R: R104.1; also elsewhere on the board
unnamed: C40.2, R42.1
unnamed: C7.1, R40.2, R45.1, U14.6 (-IN)
unnamed: C7.2, C41.1, R88.1, U14.7 (OUT)
unnamed: C48.1, R73.2, R74.1, U4.13 (-IN)
unnamed: C6.1, R20.2, R43.1, U14.2 (-IN)
unnamed: C6.2, C40.1, R87.1, U14.1 (OUT)
unnamed: C17.1, R39.1, R42.2, U14.13 (-IN)
unnamed: C18.1, R41.1, R44.2, U14.9 (-IN)
unnamed: C18.2, R41.2, R47.1, U14.8 (OUT)
unnamed: C19.1, R50.1, R58.2, U16.9 (-IN)
unnamed: C19.2, R50.2, R51.1, U16.8 (OUT)
unnamed: C24.1, R48.1, R54.2, U16.13 (-IN)
unnamed: C24.2, R48.2, R49.1, U16.14 (OUT)
unnamed: C25.1, R52.1, R57.1, R96.1, U16.2 (-IN)
unnamed: C25.2, R52.2, R54.1, U16.1 (OUT)
unnamed: C28.1, R53.1, R59.1, R97.1, U16.6 (-IN)
unnamed: C28.2, R53.2, R58.1, U16.7 (OUT)
unnamed: C41.2, R44.1
unnamed: C55.2, R57.2, R85.2, R96.2
unnamed: C56.2, R59.2, R86.2, R97.2
unnamed: C17.2, R39.2, R46.1, U14.14 (OUT)
unnamed: R45.2, R88.2
unnamed: R43.2, R87.2
unnamed: C46.1, R55.2, R56.1, U4.2 (-IN)
unnamed: C46.2, R56.2, R73.1, U4.1 (OUT)
unnamed: C47.1, R60.2, R61.1, U4.6 (-IN)
unnamed: C47.2, R61.2, R80.1, U4.7 (OUT)
unnamed: C27.1, R66.1, R101.2, U11.13 (-IN)
unnamed: C27.2, R66.2, R67.1, U11.14 (OUT)
unnamed: C49.1, R80.2, R81.1, U4.9 (-IN)
unnamed: C26.1, R71.1, R103.2, U11.9 (-IN)
unnamed: C26.2, R71.2, R72.1, U11.8 (OUT)
unnamed: C49.2, R81.2, R98.1, U4.8 (OUT)
unnamed: C48.2, R74.2, R82.1, U4.14 (OUT)
unnamed: C52.1, R99.1, R102.2, U11.2 (-IN)
unnamed: C52.2, R99.2, R101.1, U11.1 (OUT)
unnamed: C53.1, R100.1, R104.2, U11.6 (-IN)
unnamed: C53.2, R100.2, R103.1, U11.7 (OUT)

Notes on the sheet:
Audio I/O
NOTE -- the input attenuation on the PCM3060 circuit has been reduced to 9.4x to align the 1Vrms and 3Vpp inputs of the WM8731 and PCM3060.

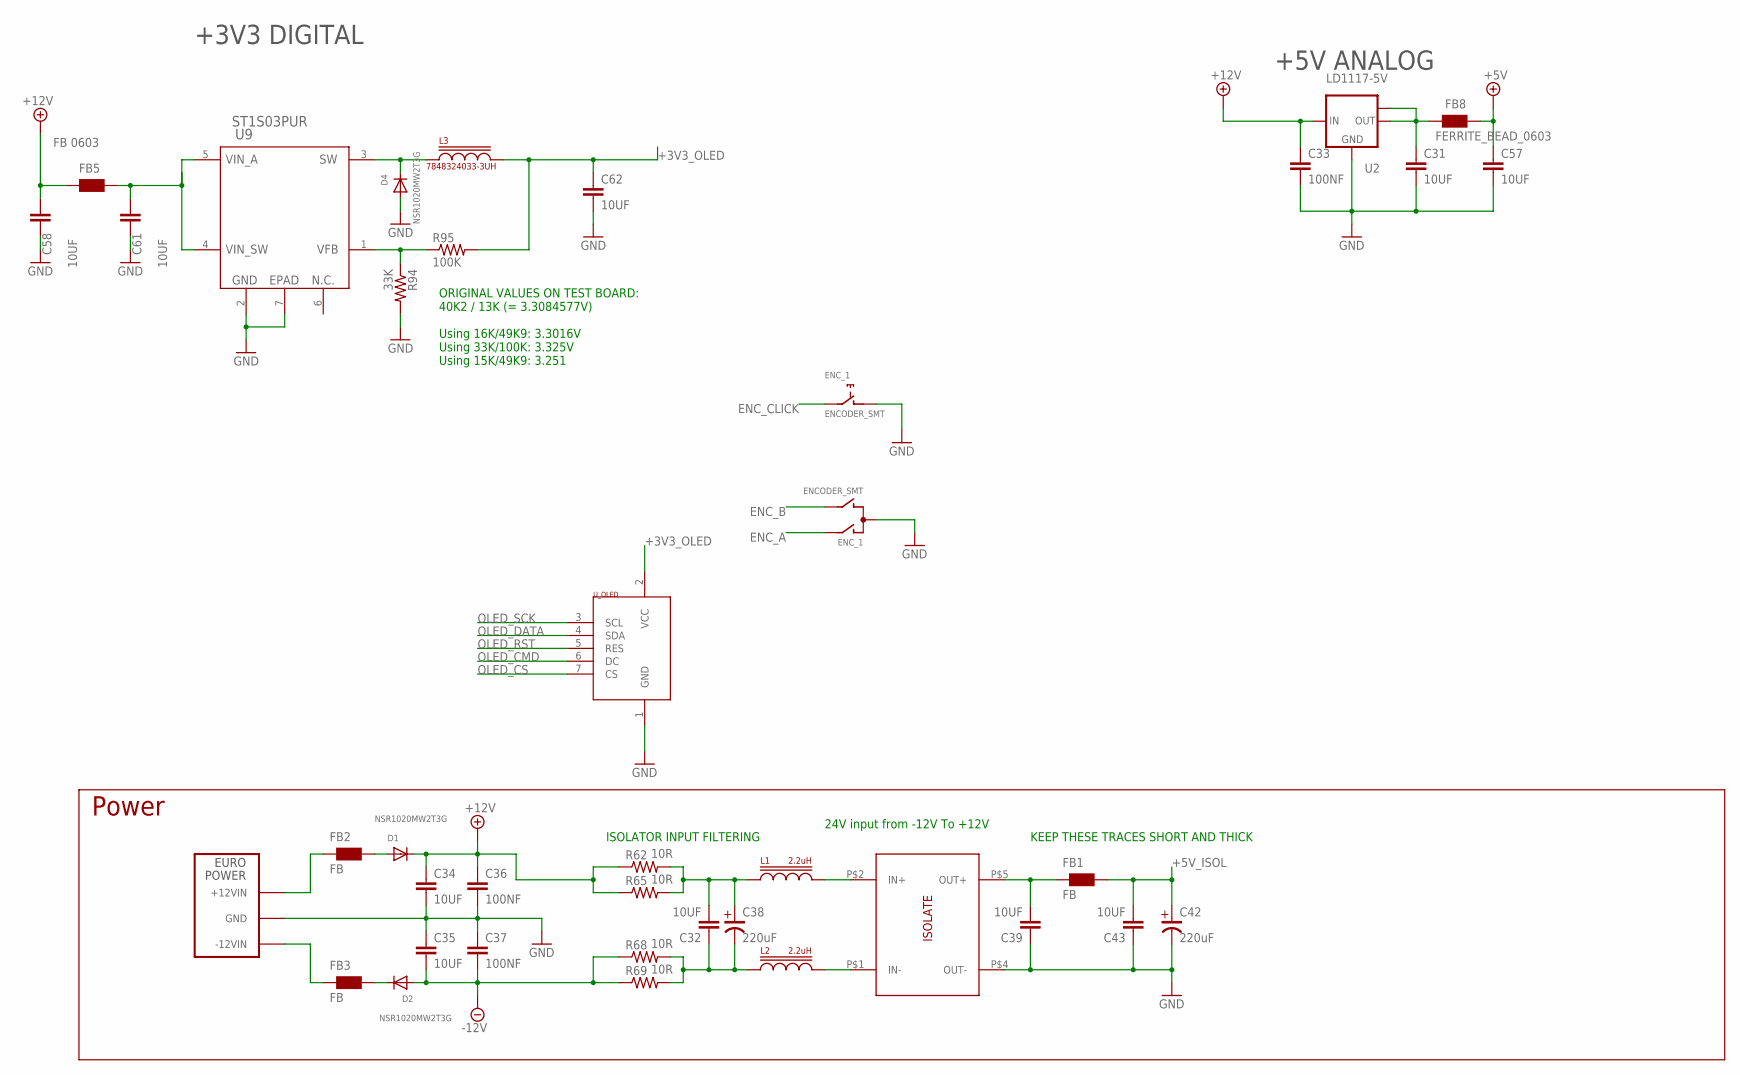
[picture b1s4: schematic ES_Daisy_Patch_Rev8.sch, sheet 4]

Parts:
C31, C32, C34, C35, C39, C43, C57, C58, C61, C62: 10UF; C0805
C33, C36, C37: 100NF; C0402
C38, C42: 220uF; PANASONIC_D
D1, D2, D4: NSR1020MW2T3G; SOD-323F
ENC_1: ENCODER_SMT; VH1-147
EP1: EURORACK_POWERSMT_2X8; 2X8_SMD_PWR
FB1, FB2, FB3: FB; WUERTH-ELEKTRONIK_0603
FB5: FB 0603; WUERTH-ELEKTRONIK_0603
FB8: FERRITE_BEAD_0603; WUERTH-ELEKTRONIK_0603
L1, L2: 2.2uH; BOURNS_SRP2010
L3: 7848324033-3UH; I1008
R62, R65, R68, R69: 10R; R0603
R94: 33K; R0603
R95: 100K; R0402
U2: LD1117-5V; SOT223
U9: ST1S03PUR; DFN06_3X3_STM
U$1: U24V/5V DC/DC ISOLATOR; XP_POWER_ISEXXXXA
U_OLED: OLED_DISPLAY; ER-OLEDM015-2

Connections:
+3V3_OLED: C62.1, L3.2, R95.2, U_OLED.2 (VCC)
+5V: C57.1, FB8.2; also elsewhere on the board
+5V_ISOL: C42.+ (POS), C43.2, FB1.2; also elsewhere on the board
+12V: C33.1, C34.1, C36.1, C58.1, D1.C, FB5.1, R62.1, R65.1, U2.3 (IN); also elsewhere on the board
-12V: C35.2, C37.2, D2.A, R68.1, R69.1; also elsewhere on the board
ENC_A: ENC_1.A; also elsewhere on the board
ENC_B: ENC_1.B; also elsewhere on the board
ENC_CLICK: ENC_1.E (2); also elsewhere on the board
GND: C31.2, C33.2, C34.2, C35.1, C36.2, C37.1, C39.1, C42.- (NEG), C43.1, C57.2, C58.2, C61.2, C62.2, D4.A, ENC_1.C, ENC_1.D (1), EP1.9 (GND), EP1.10 (GND), EP1.11 (GND), EP1.12 (GND), EP1.13 (GND), EP1.14 (GND), R94.2, U2.1 (GND), U9.2 (GND), U9.7 (EPAD), U$1.P$4 (OUT-), U_OLED.1 (GND); also elsewhere on the board
unnamed: R94.1, R95.1, U9.1 (VFB)
unnamed: D4.C, L3.1, U9.3 (SW)
unnamed: C39.2, FB1.1, U$1.P$5 (OUT+)
unnamed: L1.P$2, U$1.P$2 (IN+)
unnamed: L2.P$2, U$1.P$1 (IN-)
unnamed: C32.2, C38.+ (POS), L1.P$1, R62.2, R65.2
unnamed: C32.1, C38.- (NEG), L2.P$1, R68.2, R69.2
unnamed: C61.1, FB5.2, U9.4 (VIN_SW), U9.5 (VIN_A)
unnamed: EP1.7 (+12VIN), EP1.8 (+12VIN), FB2.1
unnamed: EP1.15 (-12VIN), EP1.16 (-12VIN), FB3.1
unnamed: D1.A, FB2.2
unnamed: D2.C, FB3.2
OLED_CMD: U_OLED.6 (DC); also elsewhere on the board
OLED_CS: U_OLED.7 (CS); also elsewhere on the board
OLED_DATA: U_OLED.4 (SDA); also elsewhere on the board
OLED_RST: U_OLED.5 (RES); also elsewhere on the board
OLED_SCK: U_OLED.3 (SCL); also elsewhere on the board
V_REG_3: C31.1, FB8.1, U2.2 (OUT), U2.TAB (OUT1)

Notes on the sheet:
Power
ISOLATOR INPUT FILTERING
24V input from -12V To +12V
KEEP THESE TRACES SHORT AND THICK
+3V3 DIGITAL
+5V ANALOG
ORIGINAL VALUES ON TEST BOARD: 40K2 / 13K (= 3.3084577V) Using 16K/49K9: 3.3016V Using 33K/100K: 3.325V Using 15K/49K9: 3.251

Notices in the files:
README.md:
- **Test input sample:** *Church bells* from [BBC Sound Effects](https://sound-effects.bbcrewind.co.uk/), © BBC, used under the [RemArc licence](https://sound-effects.bbcrewind.co.uk/licensing). Used as input to the phase vocoder resynthesis in this project’s test suite.
parts and their libraries:
COPYRIGHT: Copyright (C) 2021 Ultra Librarian. All rights reserved.
